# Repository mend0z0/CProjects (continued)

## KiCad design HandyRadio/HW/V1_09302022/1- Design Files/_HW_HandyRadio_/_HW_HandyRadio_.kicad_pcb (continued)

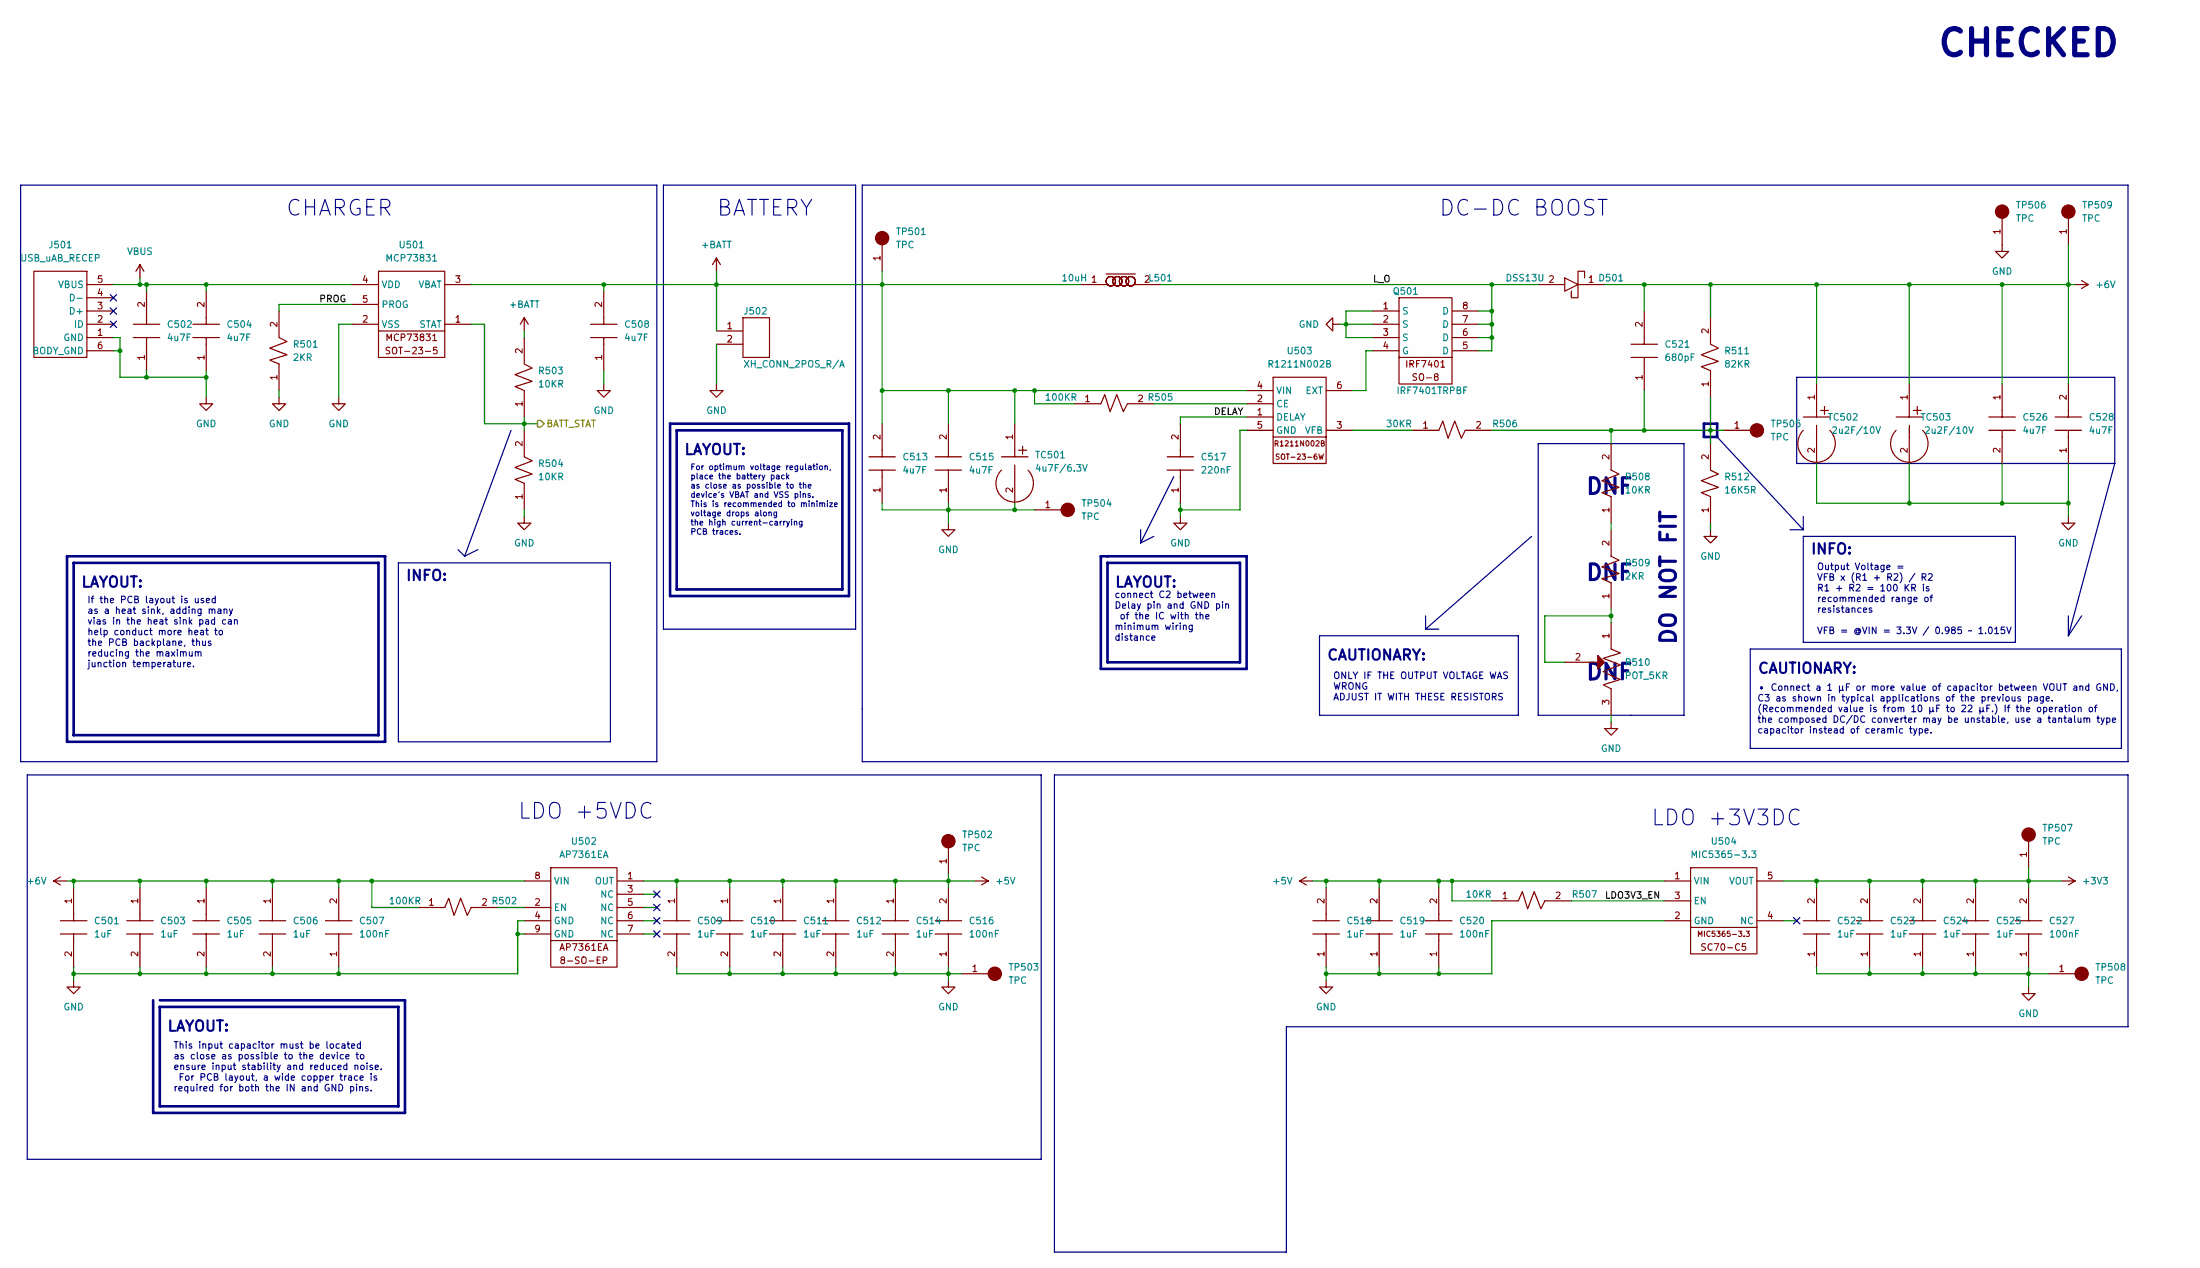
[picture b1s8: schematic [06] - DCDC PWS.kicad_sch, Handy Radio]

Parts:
C501, C503, C505, C506, C509, C510, C511, C512, C514, C518, C519, C522, C523, C524, C525: 1uF; C_0805_2012Metric_Pad1.18x1.45mm_HandSolder
C502, C504, C508, C513, C515, C526, C528: 4u7F; C_0805_2012Metric_Pad1.18x1.45mm_HandSolder
C507, C516, C520, C527: 100nF; C_0805_2012Metric_Pad1.18x1.45mm_HandSolder
C517: 220nF; C_0805_2012Metric_Pad1.18x1.45mm_HandSolder
C521: 680pF; C_0805_2012Metric_Pad1.18x1.45mm_HandSolder
D501: DSS13U; D_SOD-123F
J501: USB_uAB_RECEP; USB_Micro-AB_Molex_47590-0001
J502: XH_CONN_2POS_R/A; JST_PH_S2B-PH-K_1x02_P2.00mm_Horizontal
L501: 10uH; L_Bourns-SRN4018
Q501: IRF7401TRPBF; SOIC-8_3.9x4.9mm_P1.27mm
R501, R509: 2KR; R_0805_2012Metric_Pad1.20x1.40mm_HandSolder
R502, R505: 100KR; R_0805_2012Metric_Pad1.20x1.40mm_HandSolder
R503, R504, R507, R508: 10KR; R_0805_2012Metric_Pad1.20x1.40mm_HandSolder
R506: 30KR; R_0805_2012Metric_Pad1.20x1.40mm_HandSolder
R510: POT_5KR; Potentiometer_Bourns_TC33X_Vertical
R511: 82KR; R_0805_2012Metric_Pad1.20x1.40mm_HandSolder
R512: 16K5R; R_0805_2012Metric_Pad1.20x1.40mm_HandSolder
TC501: 4u7F/6.3V; CP_EIA-2012-12_Kemet-R_Pad1.30x1.05mm_HandSolder
TC502, TC503: 2u2F/10V; CP_EIA-2012-12_Kemet-R_Pad1.30x1.05mm_HandSolder
TP501, TP502, TP503, TP504, TP505, TP506, TP507, TP508, TP509: TPC; TestPoint_Pad_D1.5mm
U501: MCP73831; SOT-23-5
U502: AP7361EA; Infineon_PG-DSO-8-27_3.9x4.9mm_EP2.65x3mm_ThermalVias
U503: R1211N002B; SOT-23-6_Handsoldering
U504: MIC5365-3.3; SOT-353_SC-70-5_Handsoldering

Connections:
+3V3: C522.2, C523.2, C524.2, C525.2, C527.2, TP507.1, U504.5 (VOUT); also elsewhere on the board
+5V: C509.1, C510.1, C511.1, C512.1, C514.1, C516.2, C518.2, C519.2, C520.2, R507.1, TP502.1, U502.1 (OUT), U504.1 (VIN); also elsewhere on the board
+6V: C501.1, C503.1, C505.1, C506.1, C507.2, C521.2, C526.1, C528.2, D501.1, R502.1, R511.2, TC502.1, TC503.1, TP509.1, U502.8 (VIN)
+BATT: C508.2, C513.2, C515.2, J502.1, L501.1, R503.2, R505.1, TC501.1, TP501.1, U501.3 (VBAT), U503.4 (VIN)
/BLOCK DIAGRAM/DCDC PWS/DELAY: C517.2, U503.1 (DELAY)
/BLOCK DIAGRAM/DCDC PWS/LDO3V3_EN: R507.2, U504.3 (EN)
/BLOCK DIAGRAM/DCDC PWS/L_O: D501.2, L501.2, Q501.5 (D), Q501.6 (D), Q501.7 (D), Q501.8 (D)
/BLOCK DIAGRAM/DCDC PWS/PROG: R501.2, U501.5 (PROG)
/BLOCK DIAGRAM/MCU, RTC, OLED, PB, LED/BATT_STAT: R503.1, R504.2, U501.1 (STAT); also elsewhere on the board
GND: C501.2, C502.1, C503.2, C504.1, C505.2, C506.2, C507.1, C508.1, C509.2, C510.2, C511.2, C512.2, C513.1, C514.2, C515.1, C516.1, C517.1, C518.1, C519.1, C520.1, C522.1, C523.1, C524.1, C525.1, C526.2, C527.1, C528.1, J501.1 (GND), J501.6 (BODY_GND), J502.2, Q501.1 (S), Q501.2 (S), Q501.3 (S), R501.1, R504.1, R510.3, R512.1, TC501.2, TC502.2, TC503.2, TP503.1, TP504.1, TP506.1, TP508.1, U501.2 (VSS), U502.4 (GND), U502.9 (GND), U503.5 (GND), U504.2 (GND); also elsewhere on the board
unnamed: C521.1, R506.2, R508.2, R511.1, R512.2, TP505.1
unnamed: Q501.4 (G), U503.6 (EXT)
unnamed: R502.2, U502.2 (EN)
unnamed: R505.2, U503.2 (CE)
unnamed: R506.1, U503.3 (VFB)
unnamed: R508.1, R509.2
unnamed: R509.1, R510.1, R510.2
VBUS: C502.2, C504.2, J501.5 (VBUS), U501.4 (VDD)

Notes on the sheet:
LAYOUT:
BATTERY
DC-DC BOOST
ONLY IF THE OUTPUT VOLTAGE WAS WRONG ADJUST IT WITH THESE RESISTORS
For optimum voltage regulation, place the battery pack as close as possible to the device’s VBAT and VSS pins. This is recommended to minimize voltage drops along the high current-carrying PCB traces.
DO NOT FIT
INFO:
• Connect a 1 µF or more value of capacitor between VOUT and GND, C3 as shown in typical applications of the previous page. (Recommended value is from 10 µF to 22 µF.) If the operation of the composed DC/DC converter may be unstable, use a tantalum type capacitor instead of ceramic type.
CAUTIONARY:
LDO +5VDC
connect C2 between Delay pin and GND pin of the IC with the minimum wiring distance
Output Voltage = VFB x (R1 + R2) / R2 R1 + R2 = 100 KR is recommended range of resistances VFB = @VIN = 3.3V / 0.985 ~ 1.015V
This input capacitor must be located as close as possible to the device to ensure input stability and reduced noise. For PCB layout, a wide copper trace is required for both the IN and GND pins.
If the PCB layout is used as a heat sink, adding many vias in the heat sink pad can help conduct more heat to the PCB backplane, thus reducing the maximum junction temperature.
LDO +3V3DC
DNF
CHECKED
CHARGER

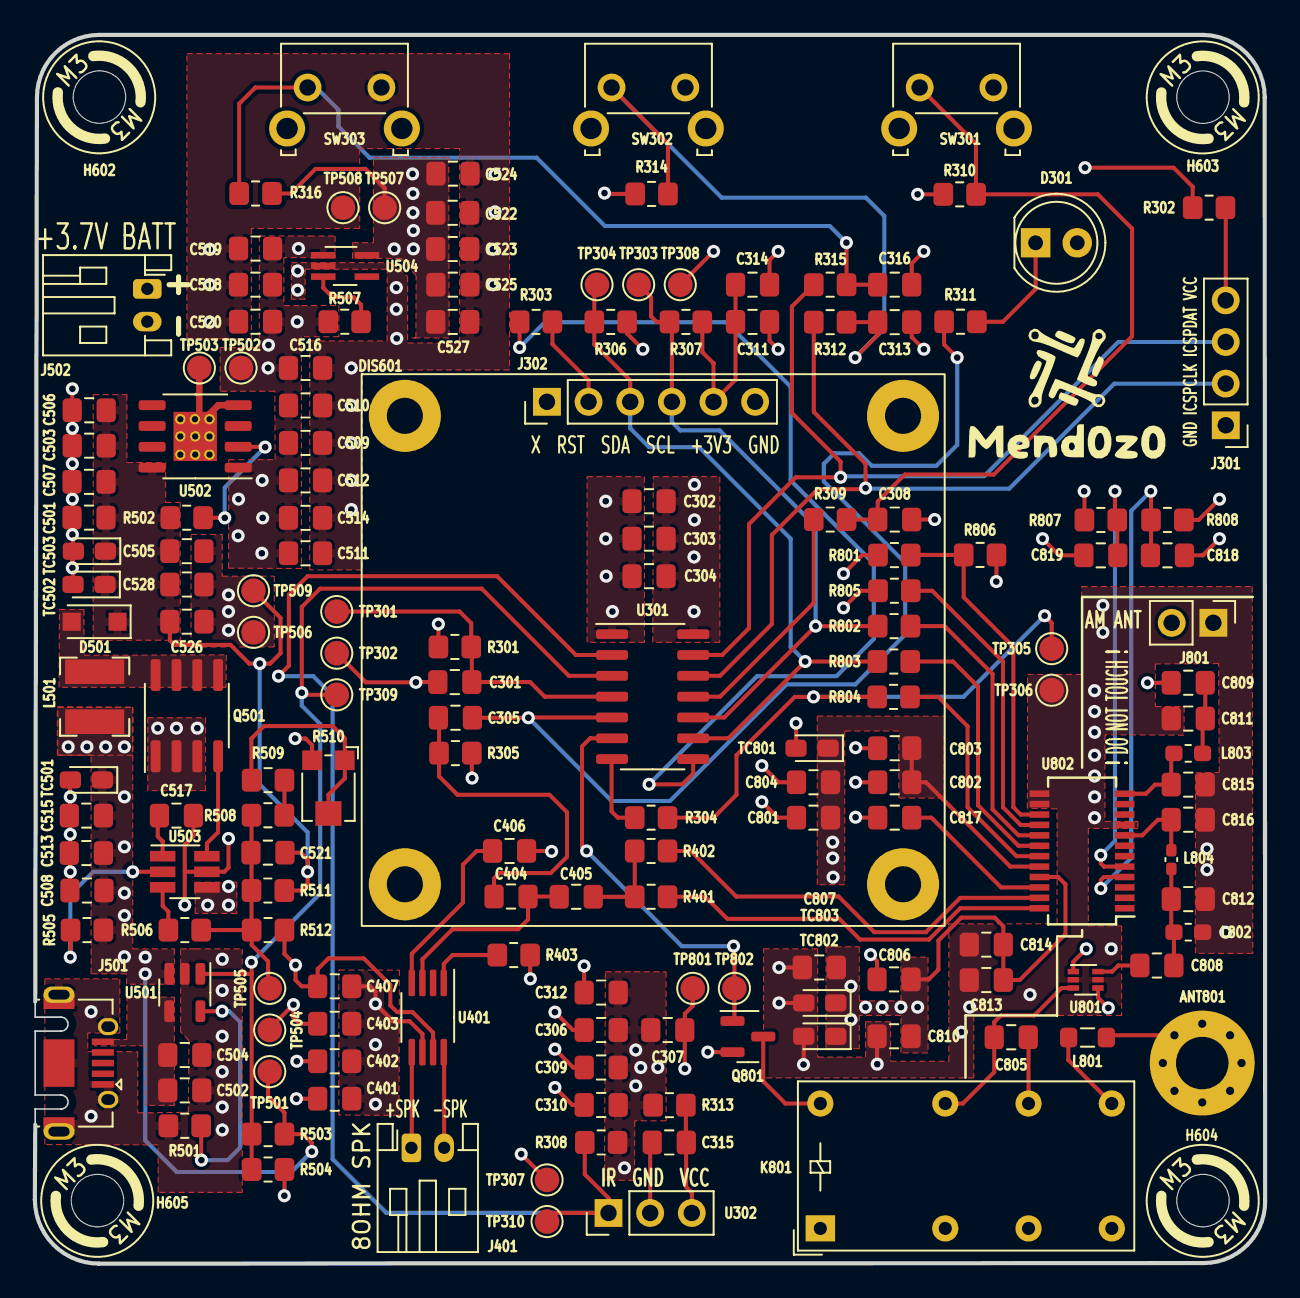
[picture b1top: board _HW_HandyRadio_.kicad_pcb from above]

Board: 4 copper layers, 75.0 x 75.0 mm, 171 parts (0 on the bottom side), 65 nets.

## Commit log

2022-09-06 Medical Watch project has been added
2022-09-06 Working on I2C peripheral
2022-09-08 BLDC Driver has been added
2022-09-11 Working on Hardware and GUI
2022-09-11 working on GUI
2022-09-12 Update on File names
2022-09-14 MEDWatch on Progress
2022-09-15 I2C bus has been opened :D
2022-09-16 SSD1306 has been done
2022-09-17 BMI160 part has started to work on
2022-09-19 Hardware Template has been modified
2022-09-19 reading data from DS1307 has been done, it's pending for testing
2022-09-19 writing data on DS1307 has been done
2022-09-19 max30102 has been created
2022-09-30 Medical Watch Hardware work on progress
2022-10-03 Adding HandyRadio to C projects
2022-10-03 HandyRadio BlockDiagram has been done
2022-10-04 1/6 of the hardware has been done
2022-10-04 2/6 HandyRadio HW has been done
2022-10-08 power supply section has been done
2022-10-09 Schematic is almost done
2022-10-11 95 SCHEMATIC HAS BEEN DONE
2022-10-11 Schematic has been double checked
2022-10-11 99% SCHEMATIC HAS BEEN DONE
2022-10-13 footprints have been added
2022-10-13 almost ready for routing and finishing PCB :D
2022-10-13 doing placement
2022-10-13 Placement is almost done
    Just it needs to checking the footprints, add some 3d and doing routing!
2022-10-14 Working on lib and pcb layout
2022-10-17 Some work on PCB, it's paused and will be continued later on
2022-10-30 serious modification has been done
2022-10-31 layout is in progress
2022-11-02 layout has been done, only checking rules has been left
2022-11-02 almost critical errors have been corrected
2022-11-02 some correction around the Antenna
2022-11-02 IT'S ALMOST GOOD FOR RELEASE, schematic should be checked and a double check on routing
2022-11-04 some modification
2022-11-06 Serious changes in placement
2022-11-06 replacement almost done, but routing left
2022-11-06 routing on progress
2022-11-08 routing has been almost done
2022-11-10 routing has finished
2022-11-10 Ready to release the HW :smile:
